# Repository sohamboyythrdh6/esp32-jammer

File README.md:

##esp32-jammer 

esp32 jammer a device that can jam your surrounding Bluetooth and Wi-Fi 

this project is seem like illegal if it misused but i made this project just for educational purpose and learning this can jam those Bluetooth and Wi-Fi and it can also jam mobile network. this is a simple esp32 based project for electronic hobbyist or iot teenagers who interested to build some kind of crazy electronic projects 

  <summary>📦 Bill of Materials (BOM)</summary>

| Component | Purpose | Qty | Cost (USD) | Distributor |
|-----------|---------|-----|------------|-------------|
| 1200mAh LiPo Battery | Powers the device | 1 | $2.53 | Maker Bazar |
| TP4056 Li-ion Battery Charger & Boost Module | Charges the battery and provides regulated output | 1 | $0.60 | Maker Bazar |
| Custom PCB | Mounts and connects all components | 1 | $20 | JLCPCB |
| WS2812 RGB LED Breakout Module | Visual status indicator | 1 | $0.19 | Robu.in |
| 12×12 Tactile Push Button | User input controls | 5 | $0.48 | Maker Bazar |
| 0.96" 128×64 OLED Display Module | Displays menus and status information | 1 | $2.00 | Maker Bazar |
| 2.4GHz NRF24L01 Module | Wireless communication module | 1 | $4.62 | Maker Bazar |
| ESP32-WROOM | Main microcontroller | 1 | $3.40 | Robu.in |
| Delivery Charges | Shipping costs | 3 | $2 | Various |

**Total Estimated Cost:** **$40USD**

if you interested to build this project so you need to buy all the components and the pcb also you need a soldering iron then solder all the parts on the pcb board as given then program the board by the code given in the repo and also connect the battery finally you are ready to use 

for use it is very simple just up and down to select the mode as you wanted to WIFI or Bluetooth then click the center button for select and then it will be started working .

                                                   !warning!
please use this device just for education purpose not to disturb others then it will be caught as illegal!

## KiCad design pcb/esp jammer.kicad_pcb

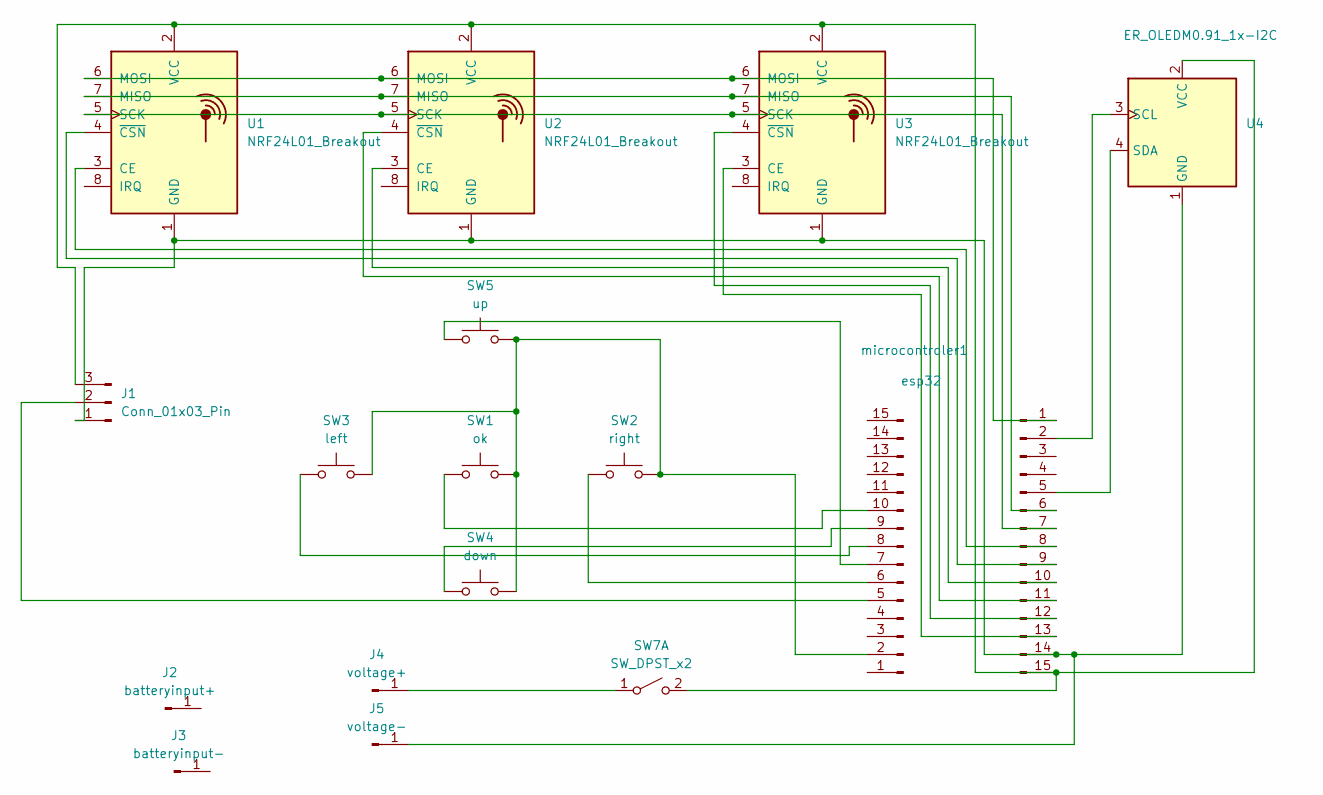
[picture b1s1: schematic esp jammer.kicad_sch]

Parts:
J1: Conn_01x03_Pin; PinSocket_1x03_P2.54mm_Vertical
J2: batteryinput+; PinHeader_1x01_P1.00mm_Vertical
J3: batteryinput-; PinHeader_1x01_P1.00mm_Vertical
J4: voltage+; PinHeader_1x01_P1.00mm_Vertical
J5: voltage-; PinHeader_1x01_P1.00mm_Vertical
SW1: ok; SW_PUSH-12mm
SW2: right; SW_PUSH-12mm
SW3: left; SW_PUSH-12mm
SW4: down; SW_PUSH-12mm
SW5: up; SW_PUSH-12mm
SW7: SW_DPST_x2; SW_Slide_SPDT_Angled_CK_OS102011MA1Q
U1, U2, U3: NRF24L01_Breakout; nRF24L01_Breakout
U4: ER_OLEDM0.91_1x-I2C
esp32: Conn_01x15_Pin; PinSocket_1x15_P2.54mm_Vertical_SMD_Pin1Left
microcontroler1: Conn_01x15_Pin; PinSocket_1x15_P2.54mm_Vertical_SMD_Pin1Left

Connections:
unnamed: J1.1, J5.1 (Pin_1_1), U1.1 (GND), U2.1 (GND), U3.1 (GND), U4.1 (GND), esp32.14
unnamed: J1.2, microcontroler1.5
unnamed: J1.3, SW7.2 (B), U1.2 (VCC), U2.2 (VCC), U3.2 (VCC), U4.2 (VCC), esp32.15
unnamed: J4.1 (Pin_1_1), SW7.1 (A)
unnamed: U1.3 (CE), esp32.8
unnamed: U1.7 (MISO), U2.7 (MISO), U3.7 (MISO), esp32.6
unnamed: U1.6 (MOSI), U2.6 (MOSI), U3.6 (MOSI), esp32.1
unnamed: U1.5 (SCK), U2.5 (SCK), U3.5 (SCK), esp32.7
unnamed: U1.4 (~CSN), esp32.9
unnamed: U2.3 (CE), esp32.10
unnamed: U2.4 (~CSN), esp32.11
unnamed: U3.3 (CE), esp32.13
unnamed: U3.4 (~CSN), esp32.12
unnamed: U4.3 (SCL), esp32.2
unnamed: U4.4 (SDA), esp32.5
unnamed: SW1.2, SW2.2, SW3.2, SW4.2, SW5.2, microcontroler1.2
unnamed: SW2.1, microcontroler1.6
unnamed: SW5.1, microcontroler1.7
unnamed: SW3.1, microcontroler1.8
unnamed: SW4.1, microcontroler1.9
unnamed: SW1.1, microcontroler1.10

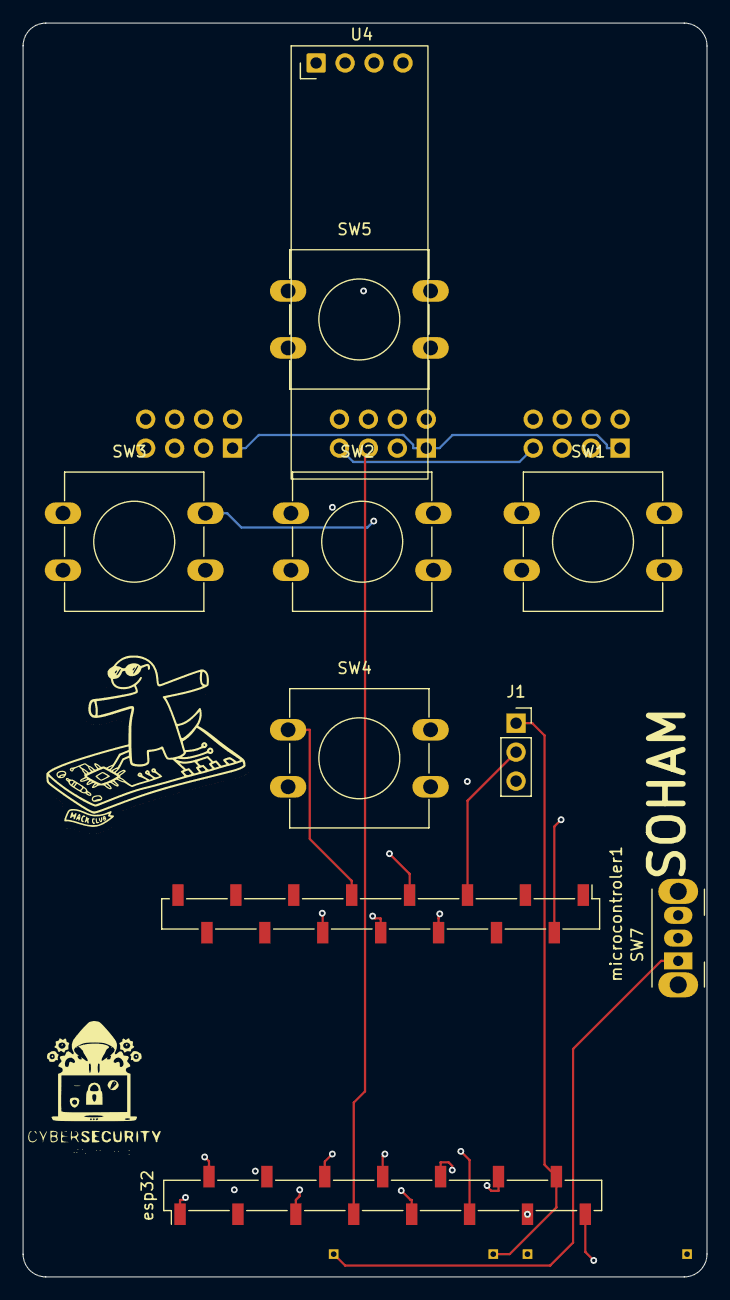
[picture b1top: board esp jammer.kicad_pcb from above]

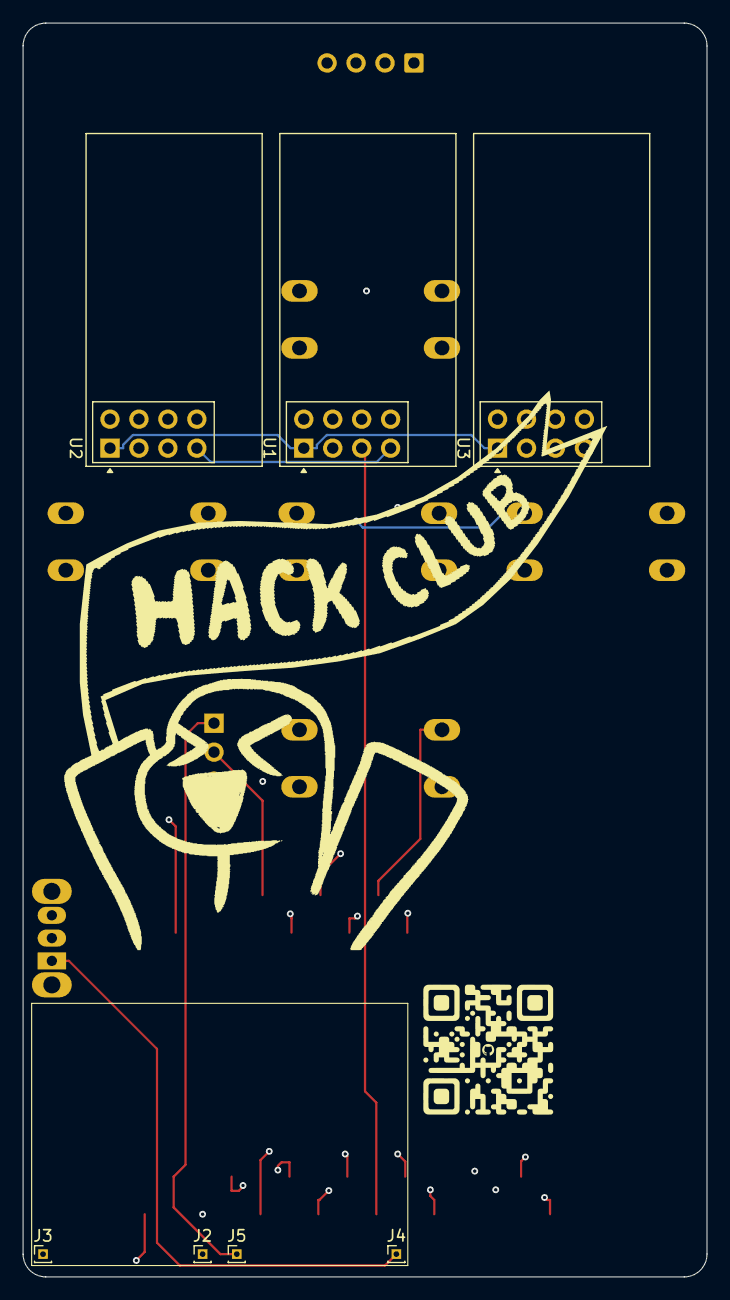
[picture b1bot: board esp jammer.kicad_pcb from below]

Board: 4 copper layers, 60.0 x 110.0 mm, 21 parts (9 on the bottom side), 21 nets.

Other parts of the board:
dddd: LOGO
dddddfff: LOGO
fffff: LOGO
ffghhhj: LOGO

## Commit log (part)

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2026-06-29 Create b
2026-06-29 Create 5
